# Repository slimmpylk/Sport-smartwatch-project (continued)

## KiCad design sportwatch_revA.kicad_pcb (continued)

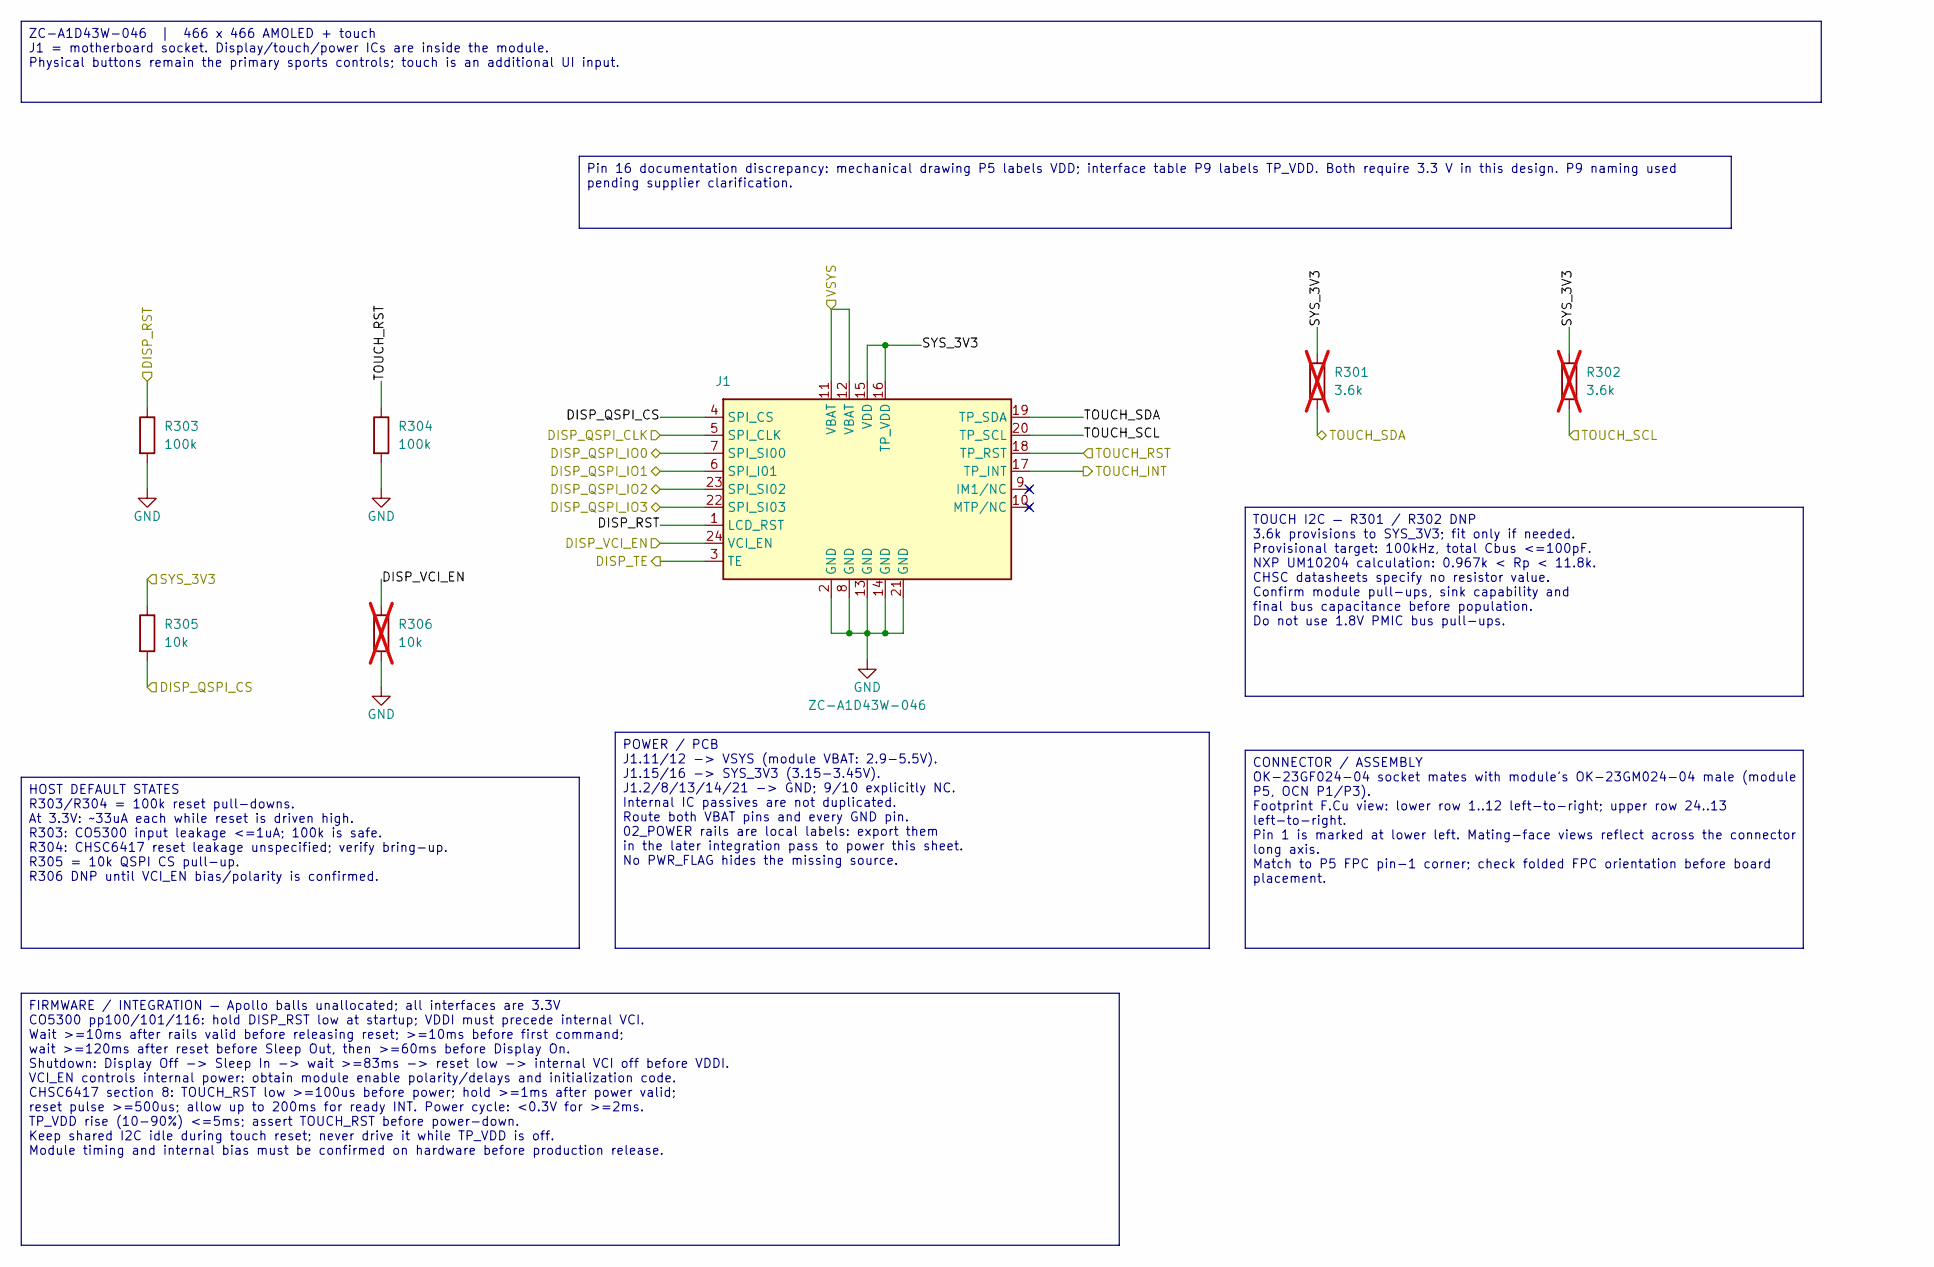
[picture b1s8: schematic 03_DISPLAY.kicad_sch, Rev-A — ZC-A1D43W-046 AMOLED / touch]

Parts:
J1: ZC-A1D43W-046; OK-23GF024-04; MPN OK-23GF024-04
R301, R302: 3.6k; R_0402_1005Metric; Tolerance 1%; Rating 0.063W, >=25V; not fitted
R303, R304: 100k; R_0402_1005Metric; Tolerance 1%; Rating 0.063W, >=25V
R305: 10k; R_0402_1005Metric; Tolerance 1%; Rating 0.063W, >=25V
R306: 10k; R_0402_1005Metric; Tolerance 1%; Rating 0.063W, >=25V; not fitted

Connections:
/DISP_QSPI_CLK: J1.5 (SPI_CLK); also elsewhere on the board
/DISP_QSPI_CS: J1.4 (SPI_CS), R305.2; also elsewhere on the board
/DISP_QSPI_IO0: J1.7 (SPI_SI00); also elsewhere on the board
/DISP_QSPI_IO1: J1.6 (SPI_I01); also elsewhere on the board
/DISP_QSPI_IO2: J1.23 (SPI_SI02); also elsewhere on the board
/DISP_QSPI_IO3: J1.22 (SPI_SI03); also elsewhere on the board
/DISP_RST: J1.1 (LCD_RST), R303.1; also elsewhere on the board
/DISP_TE: J1.3 (TE); also elsewhere on the board
/DISP_VCI_EN: J1.24 (VCI_EN), R306.1; also elsewhere on the board
/SYS_3V3: J1.15 (VDD), J1.16 (TP_VDD), R301.1, R302.1, R305.1; also elsewhere on the board
/TOUCH_INT: J1.17 (TP_INT); also elsewhere on the board
/TOUCH_RST: J1.18 (TP_RST), R304.1; also elsewhere on the board
/TOUCH_SCL: J1.20 (TP_SCL), R302.2; also elsewhere on the board
/TOUCH_SDA: J1.19 (TP_SDA), R301.2; also elsewhere on the board
/VSYS: J1.11 (VBAT), J1.12 (VBAT); also elsewhere on the board
GND: J1.2 (GND), J1.8 (GND), J1.13 (GND), J1.14 (GND), J1.21 (GND), R303.2, R304.2, R306.2; also elsewhere on the board

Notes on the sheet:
POWER / PCB J1.11/12 -> VSYS (module VBAT: 2.9-5.5V). J1.15/16 -> SYS_3V3 (3.15-3.45V). J1.2/8/13/14/21 -> GND; 9/10 explicitly NC. Internal IC passives are not duplicated. Route both VBAT pins and every GND pin. 02_POWER rails are local labels: export them in the later integration pass to power th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
CONNECTOR / ASSEMBLY OK-23GF024-04 socket mates with module's OK-23GM024-04 male (module P5, OCN P1/P3). Footprint F.Cu view: lower row 1..12 left-to-right; upper row 24..13 left-to-right. Pin 1 is marked at lower left. Mating-face views reflect across the connector long axis. Match to P5 FPC pin-1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
Pin 16 documentation discrepancy: mechanical drawing P5 labels VDD; interface table P9 labels TP_VDD. Both require 3.3 V in this design. P9 naming used pending supplier clarification.
ZC-A1D43W-046 | 466 x 466 AMOLED + touch J1 = motherboard socket. Display/touch/power ICs are inside the module. Physical buttons remain the primary sports controls; touch is an additional UI input.
TOUCH I2C — R301 / R302 DNP 3.6k provisions to SYS_3V3; fit only if needed. Provisional target: 100kHz, total Cbus <=100pF. NXP UM10204 calculation: 0.967k < Rp < 11.8k. CHSC datasheets specify no resistor value. Confirm module pull-ups, sink capability and final bus capacitance before population. 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
HOST DEFAULT STATES R303/R304 = 100k reset pull-downs. At 3.3V: ~33uA each while reset is driven high. R303: CO5300 input leakage <=1uA; 100k is safe. R304: CHSC6417 reset leakage unspecified; verify bring-up. R305 = 10k QSPI CS pull-up. R306 DNP until VCI_EN bias/polarity is confirmed.
FIRMWARE / INTEGRATION — Apollo balls unallocated; all interfaces are 3.3V CO5300 pp100/101/116: hold DISP_RST low at startup; VDDI must precede internal VCI. Wait >=10ms after rails valid before releasing reset; >=10ms before first command; wait >=120ms after reset before Sleep Out, then >=60ms be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

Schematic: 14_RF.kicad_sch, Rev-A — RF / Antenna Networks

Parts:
AE1401: ANT_BLE_2G4_TBD
AE1410: ANT_WIFI_2G4_5G_TBD
AE1420: ANT_GNSS_L1_L5_TBD
C1401: 18pF; C_0201_0603Metric
C1402: 2.8pF; C_0201_0603Metric
C1403: 3.2pF; C_0201_0603Metric
C1404: 1.0pF DNP; C_0201_0603Metric; not fitted
C1405: 220pF; C_0201_0603Metric
C1410, C1411, C1420, C1421: DNP; C_0201_0603Metric; not fitted
L1401: 1.5nH; L_0201_0603Metric
L1402: 1.8nH; L_0201_0603Metric
R1401: 0R (Lm2 tune); R_0201_0603Metric
R1410, R1420: 0R; R_0201_0603Metric
TP1401: BLE_RF_TEST_TBD
TP1410: WIFI_RF_TEST_TBD
TP1420: GNSS_RF_TEST_TBD

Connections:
/14_RF/BLE_RF_50R: AE1401.1, C1405.2, TP1401.1
/14_RF/GNSS_ANT_50R: AE1420.1, C1421.1, R1420.2, TP1420.1
/14_RF/WIFI_ANT_50R: AE1410.1, C1411.1, R1410.2, TP1410.1
/APOLLO_BLE_ANT: C1402.1, L1401.1, L1402.1; also elsewhere on the board
/APOLLO_BLE_AVDD_PA: C1401.1, L1401.2; also elsewhere on the board
/GNSS_RF: C1420.1, R1420.1; also elsewhere on the board
/WIFI_RF: C1410.1, R1410.1
GND: C1401.2, C1402.2, C1403.2, C1404.2, C1410.2, C1411.2, C1420.2, C1421.2; also elsewhere on the board
unnamed: C1403.1, L1402.2, R1401.1
unnamed: C1404.1, C1405.1, R1401.2

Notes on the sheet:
If the final 50-mm-class mechanics cannot support three independent antennas, BLE/Wi-Fi sharing may be reconsidered, but that requires a deliberate RF switch/diplexer redesign; do not silently merge the feeds.
Exact BLE/Wi-Fi/GNSS antennas are selected before routing is frozen, after the board outline, display, battery, case/bezel and available perimeter/ground-clearance regions are known.
Child-sheet labels APOLLO_BLE_ANT / APOLLO_BLE_AVDD_PA / WIFI_RF / GNSS_RF must be exported through the final hierarchy integration.
TP1401/TP1410/TP1420 are electrically attached RF test PROVISIONS; implement as tiny low-stub probe/coax-switch structures during PCB RF layout.
All RF paths must be controlled 50-ohm transmission lines with continuous reference ground, short feeds, via fencing where appropriate, and no unrelated routing through antenna keepouts.
MAX-F10S RF_IN is internally DC-blocked and requires a 50-ohm feed. No extra DC-block capacitor or active-antenna bias network is fitted for the passive Rev-A baseline.
BLE initial values are tuning STARTING POINTS only: LDC 1.5nH, Cdc1 18pF, Lm1 2.4nH, Cm1 2.0pF, Cm2 2.0pF, Cm3 DNP, Cc1 220pF. Final values require VNA/RF tuning on the real watch geometry.
nRF7002 Wi-Fi 2.4 / 5 GHz — WIFI_RF is already after the Nordic diplexer on 06_WIFI
14_RF — ANTENNA INTERFACES / MATCHING / TUNING — REV A
APOLLO510B BLE 2.4 GHz
BLE R1401 is the optional Lm2 position populated as 0R for Rev-A baseline; C1402 is on ANT/Lm1 input, C1403 at Lm1/Lm2 junction, C1404 DNP at Lm2 output.
Wi-Fi and GNSS use DNP/0R/DNP pi footprints so the antenna feed can be tuned without a PCB respin. Exact capacitor/series element values are selected after antenna and enclosure freeze.
Wi-Fi: 06_WIFI already combines nRF7002 TXRF0/TXRF1 through the Nordic 2.4/5GHz diplexer. 14_RF therefore starts from the single WIFI_RF feed.
Exact antenna MPNs/footprints are intentionally frozen only after case + PCB outline + battery + display geometry are known.
BLE: N1 BLE_ANT is single-ended RF; M1 BLE_AVDD_PA feeds the PA bias network. L1401/C1401 and the matching chain follow Ambiq's published initial BLE topology.
MAX-F10S GNSS L1/L5 — passive dual-band antenna baseline
Keep GNSS especially far from display clocks, Wi-Fi, switching regulators and haptic currents. Final antenna placements/keepouts are mechanical + RF decisions, not schematic-only decisions.

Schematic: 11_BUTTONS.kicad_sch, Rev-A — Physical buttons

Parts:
C1101, C1102, C1103, C1104, C1105: 47nF; C_0402_1005Metric
R1101, R1102, R1103, R1104, R1105: 100k; R_0402_1005Metric
SW1: BTN_LIGHT
SW2: BTN_UP
SW3: BTN_DOWN
SW4: BTN_START
SW5: BTN_BACK

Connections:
/BTN_BACK_N: C1105.1, R1105.2, SW5.1; also elsewhere on the board
/BTN_DOWN_N: C1103.1, R1103.2, SW3.1; also elsewhere on the board
/BTN_LIGHT_N: C1101.1, R1101.2, SW1.1; also elsewhere on the board
/BTN_START_N: C1104.1, R1104.2, SW4.1; also elsewhere on the board
/BTN_UP_N: C1102.1, R1102.2, SW2.1; also elsewhere on the board
GND: C1101.2, C1102.2, C1103.2, C1104.2, C1105.2, SW1.2, SW2.2, SW3.2, SW4.2, SW5.2; also elsewhere on the board
VOUT1_1V8: R1101.1, R1102.1, R1103.1, R1104.1, R1105.1; also elsewhere on the board

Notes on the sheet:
Switch footprints intentionally TBD until the exact sealed side-actuated tact switch / mechanical plunger stack is selected.
Each input has a 100k external pull-up to VOUT1_1V8 and 47nF hardware filter. Firmware should still debounce.
Apollo510B GPIO input leakage is max 20nA, so 100k pull-ups retain very large DC noise margin.
Do not rely on button labels as final GPIO ball assignments; those are frozen only during the Apollo integration pass.
100k + 47nF gives tau ~= 4.7ms (release threshold ~5.7ms for a 0.7*VDD GPIO VIH).
11_BUTTONS — FIVE PHYSICAL WATCH BUTTONS — ACTIVE LOW
No exposed electrical button contacts are assumed. If the final mechanical design creates an external conductive ESD path, add local ESD protection after mechanical review.
Final Apollo510B assignment: choose GPIOs valid in the selected low-power mode and configure falling-edge wake/interrupt.
Electrical behavior: unpressed = HIGH. Pressed = LOW. At 1.8V / 100k, a held button draws ~18uA.

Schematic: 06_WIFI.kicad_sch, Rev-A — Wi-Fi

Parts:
C601, C602, C606, C611: 4.7uF; C_0603_1608Metric
C603: 220nF; C_0201_0603Metric
C604, C614: 470nF; C_0201_0603Metric
C605, C610, C616, C619: 1.0uF; C_0402_1005Metric
C607, C618: 2.2uF; C_0603_1608Metric
C608: 10nF; C_0201_0603Metric
C609: 2.2uF; C_0402_1005Metric
C612, C617: 100nF; C_0201_0603Metric
C613: 22nF; C_0201_0603Metric
C615: 2.2uF; C_0201_0603Metric
L601: 3.3uH_1A_DCR<=200mR; L_2016_2016Metric
R601, R602: 100k; R_0402_1005Metric
U9: NRF7002-QFAA-R7; QFN48_6X6_NOR
U10: 2.4/5GHz_DIPLEXER_TBD
U11: TPS22918DBVT; SOT-23-6
Y1: NX1612SA-40M-EXS00A-CS14264; Crystal_1612-4Pin_1.6x1.2mm

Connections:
/06_WIFI/WIFI_IOVDD_1V8: C618.2, U9.48 (IOVDD), U11.6 (VOUT)
/06_WIFI/WIFI_PWRIOVDD: C609.2, C617.1, U9.1 (OTPVDD), U9.34 (PWRIOVDD)
/06_WIFI/WIFI_VDD_BUCK: C602.1, C603.1, C604.2, L601.2, U9.15 (RFBUCKVDD), U9.32 (PWRBUCKVDD)
/WIFI_BUCKEN: R601.1, U9.30 (BUCKEN); also elsewhere on the board
/WIFI_COEX_GRANT: U9.43 (COEX_GRANT); also elsewhere on the board
/WIFI_COEX_REQ: U9.42 (COEX_REQ); also elsewhere on the board
/WIFI_COEX_STATUS: U9.41 (COEX_STATUS0); also elsewhere on the board
/WIFI_HOST_IRQ: U9.46 (HOST_IRQ); also elsewhere on the board
/WIFI_IOVDD_EN: R602.2, U11.3 (ON); also elsewhere on the board
/WIFI_QSPI_CLK: U9.35 (QSPI_CLK); also elsewhere on the board
/WIFI_QSPI_CS: U9.36 (QSPI_SS); also elsewhere on the board
/WIFI_QSPI_IO0: U9.37 (QSPI_DATA0); also elsewhere on the board
/WIFI_QSPI_IO1: U9.38 (QSPI_DATA1); also elsewhere on the board
/WIFI_QSPI_IO2: U9.39 (QSPI_DATA2); also elsewhere on the board
/WIFI_QSPI_IO3: U9.40 (QSPI_DATA3); also elsewhere on the board
GND: C601.2, C602.2, C603.2, C604.1, C605.2, C606.2, C607.1, C608.2, C609.1, C610.1, C611.2, C612.2, C613.2, C614.2, C615.2, C616.2, C617.2, C618.1, C619.2, R601.2, R602.1, U9.27 (BUCKVSS), U9.28 (BUCKVSS), U9.47 (VSS), U9.49 (VSS), U10.2 (GND), U10.5 (GND), U10.7 (GND), U11.2 (GND), Y1.2 (GND), Y1.4 (GND); also elsewhere on the board
unnamed: C616.1, U9.19 (AFELDO)
unnamed: L601.1, U9.26 (BUCKOUT)
unnamed: C608.1, U9.29 (BUCKVMID)
unnamed: C610.2, U9.33 (DIGVDD)
unnamed: C611.1, U9.12 (PALDO)
unnamed: C612.1, U9.8 (PAVDD<1>), U9.10 (PAVDD<0>)
unnamed: C613.1, U9.14 (RFVDD)
unnamed: C614.1, U9.11 (SXLDO)
unnamed: C615.1, U9.16 (XOLDO)
unnamed: U9.18 (XON), Y1.3
unnamed: U9.17 (XOP), Y1.1
unnamed: U9.9 (TXRF<0>), U10.1 (2.4G)
unnamed: U9.7 (TXRF<1>), U10.3 (5G)
VBAT: C601.1, C605.1, C606.1, C607.2, U9.13 (VBAT), U9.20 (AFEVBAT), U9.25 (BUCKVBAT), U9.31 (BUCKVBATS); also elsewhere on the board
VOUT1_1V8: C619.1, U11.1 (VIN); also elsewhere on the board

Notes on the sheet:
QFN exposed pad pin49 + pin47 VSS are grounded. QFN48_6X6_NOR footprint must be audited before PCB layout.
U10: required 2.4/5 GHz WLAN diplexer; exact MPN/footprint TBD and selected together with 14_RF.
06_WIFI — nRF7002-QFAA-R7 DUAL-BAND WI-FI 6 — REV A
COEX_STATUS/REQ/GRANT kept for Wi-Fi/BLE coexistence; SW_CTRL0/1 NC with dedicated Wi-Fi antenna.
Nordic QFN reference capacitor values/package classes are reproduced; exact capacitor MPN/derating is checked at BOM/footprint audit.
IMPORTANT: nRF7002 main rail = protected-cell VBAT, NOT nPM1300 VSYS (VSYS can rise near 5 V on VBUS; nRF7002 VBAT recommended max 4.5 V).
WIFI_RF goes to 14_RF. Keep TXRF/diplexer/antenna path very short and copy Nordic RF layout closely.
C601/C602/C604/C608 ground returns must follow Nordic isolated-metal-plane guidance near the exposed paddle.
Use protected-cell VBAT for nRF7002 main supply. Do NOT substitute VSYS: nPM1300 can connect VSYS to ~5 V VBUS.
TPS22918 U11 switches 1.8 V IOVDD. QOD open; CT open. R602 and R601 hold IOVDD/BUCKEN off during Apollo reset.
Power sequence: VBAT present -> wait >=6 ms -> BUCKEN=1 -> wait >=1 ms -> IOVDD_EN=1. Power-down: BUCKEN=0 + IOVDD off before main battery rail disappears.
QSPI baseline, max interface clock 32 MHz. Final Apollo peripheral/ball allocation is deferred.
Wi-Fi must be disabled below nRF7002 VBAT minimum 2.9 V. Battery target is nominal 3.7 V / ~4.2 V full.
Nordic QFN reference network / QSPI host / 3-wire BLE coexistence / dedicated Wi-Fi antenna baseline
Y1: 40 MHz, SMD1612, CL=8 pF, ESR <=100 ohm. Exact crystal MPN/footprint TBD.
U10 is still a placeholder: current symbol pins 2/5/7 are grounded. Confirm COM, 2.4G, 5G and all GND pad numbers against the selected diplexer datasheet before PCB freeze.

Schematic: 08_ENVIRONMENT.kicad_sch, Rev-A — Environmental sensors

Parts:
C801, C802, C803, C804: 100nF; C_0402_1005Metric
R801, R802: 4.7k; R_0402_1005Metric
R803: 10k; R_0402_1005Metric
U4: BMP585; LGA9_BMP585_BOS
U5: OPT4001DTSR; DTS0008A-MFG
U6: MAX30208CLB+T; 21-100265_MXM

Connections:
ALS_INT: R803.2, U5.7 (INT); also elsewhere on the board
BARO_INT: U4.5 (INT); also elsewhere on the board
ENV_I2C_SCL: R802.2, U4.1 (SCX), U5.5 (SCL); also elsewhere on the board
ENV_I2C_SDA: R801.2, U4.2 (SDX), U5.8 (SDA), U6.8 (SDA); also elsewhere on the board
GND: C801.2, C802.2, C803.2, C804.2, U4.3 (SDO), U4.6 (VSS), U5.2 (ADDR), U5.4 (GND), U6.4 (GND), U6.5 (GND), U6.6 (GND), U6.7 (GPIO1), U6.10 (GPIO0); also elsewhere on the board
VOUT1_1V8: C801.1, C802.1, C803.1, C804.1, R801.1, R802.1, R803.1, U4.4 (VDDIO), U4.7 (CSB), U4.8 (VDD), U5.1 (VDD), U6.1 (VDD), U6.2 (VDD), U6.3 (VDD); also elsewhere on the board

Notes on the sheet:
POWER / BUS PULL-UPS
R801/R802 = 4.7k pull-ups for provisional 400 kHz short sensor bus. Consolidate pull-ups if this bus is later shared with BMM350/PMIC.
MAX30208: GPIO1=GND and GPIO0=GND => fixed 7-bit address 0x50; temperature is polled, no interrupt pin consumed.
BMP585 mechanical: pressure port must breathe through a hydrophobic/ePTFE vent; never cover the port with adhesive or conformal coating.
08_ENVIRONMENT — BMP585 BAROMETER + MAX30208 SKIN TEMPERATURE + OPT4001 AMBIENT LIGHT — REV A
OPT4001 mechanical: provide a real optical window / bezel opening; do not place behind opaque AMOLED or black mask.
All three sensors use VOUT1_1V8. ENV_I2C_SDA/SCL are a 1.8 V I2C bus; Apollo pin assignment is deferred.
OPT4001DTSR: ADDR=GND => 0x44; ALS_INT is open-drain and uses R803=10k pull-up. C801=100nF at VDD.
MAX30208 placement: skin-facing and thermally isolated from PMIC/SoC/PPG LEDs; thin traces/cutouts or flex improve skin tracking.
BMP585: I2C mode; CSB=1.8 V, SDO=GND => 7-bit address 0x46; BARO_INT reserved for data-ready/interrupt.
BMP585: C803/C804 = 100nF at VDDIO/VDD. If either rail ramps faster than 10 us, Bosch recommends 10 ohm series limiting.

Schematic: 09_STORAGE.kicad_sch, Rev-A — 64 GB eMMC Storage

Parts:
C901: 4.7uF; C_0603_1608Metric
C902: 220nF; C_0402_1005Metric
C903: 2.2uF; C_0603_1608Metric
C904, C906: 100nF; C_0402_1005Metric
C905: 1.0uF; C_0402_1005Metric
R901: 10k; R_0402_1005Metric
R902, R903, R904, R905, R906, R907, R908, R909, R910: 47k; R_0402_1005Metric
U901: EMMC64G-TB9F-06011; FBGA-153_8.0x8.5mm_Layout14x14_P0.5mm

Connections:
/09_STORAGE/EMMC_VDDI: C905.1, C906.1, U901.C2 (VDDI)
/EMMC_CLK: U901.M6 (CLK); also elsewhere on the board
/EMMC_CMD: R901.2, U901.M5 (CMD); also elsewhere on the board
/EMMC_DAT0: R902.2, U901.A3 (DAT0); also elsewhere on the board
/EMMC_DAT1: R903.2, U901.A4 (DAT1); also elsewhere on the board
/EMMC_DAT2: R904.2, U901.A5 (DAT2); also elsewhere on the board
/EMMC_DAT3: R905.2, U901.B2 (DAT3); also elsewhere on the board
/EMMC_DAT4: R906.2, U901.B3 (DAT4); also elsewhere on the board
/EMMC_DAT5: R907.2, U901.B4 (DAT5); also elsewhere on the board
/EMMC_DAT6: R908.2, U901.B5 (DAT6); also elsewhere on the board
/EMMC_DAT7: R909.2, U901.B6 (DAT7); also elsewhere on the board
/EMMC_RST_N: R910.2, U901.K5 (~RST_n); also elsewhere on the board
/VOUT2_3V0_PROVISIONAL: C901.1, C902.1, U901.E6 (VCC), U901.F5 (VCC), U901.J10 (VCC), U901.K9 (VCC); also elsewhere on the board
GND: C901.2, C902.2, C903.2, C904.2, C905.2, C906.2, U901.A6 (VSS), U901.C4 (VSSQ), U901.E7 (VSS), U901.G5 (VSS), U901.H10 (VSS), U901.J5 (VSS), U901.K8 (VSS), U901.N2 (VSSQ), U901.N5 (VSSQ), U901.P4 (VSSQ), U901.P6 (VSSQ); also elsewhere on the board
VOUT1_1V8: C903.1, C904.1, R901.1, R902.1, R903.1, R904.1, R905.1, R906.1, R907.1, R908.1, R909.1, R910.1, U901.C6 (VCCQ), U901.M4 (VCCQ), U901.N4 (VCCQ), U901.P3 (VCCQ), U901.P5 (VCCQ); also elsewhere on the board

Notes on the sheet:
RFU/VSF/NC balls remain unconnected exactly as Kingston requires. Footprint is intentionally still unassigned pending the dedicated FBGA153 footprint audit.
Kingston states DAT1-DAT7 internal pull-ups are disconnected after entering wide-bus modes, so external biasing remains useful.
Kingston's public datasheet calls for an external VDDI Creg but refers exact design values to a separate design guide; capacitor values use standard eMMC guidance.
09_STORAGE — 64 GB eMMC / APOLLO510B SDIO0 8-BIT — REV A
Architecture: Apollo510B SDIO0 is reserved for this eMMC because SDIO0 supports the full 8-bit eMMC bus.
EMMC_RST_N uses a normal Apollo GPIO; hardware reset is disabled by default in eMMC and must be enabled through EXT_CSD if used.
Add/tune a small CLK source-series resistor near Apollo during 01_APOLLO integration (22 ohm initial target); keep it physically at the host, not beside U1.
Apollo510B documents SDIO0 up to 96 MHz / 96 MB/s. Therefore U1 is NOT operated in HS400; H5/DS is intentionally NC.
Place U1 close to Apollo. Route CLK/CMD/DAT0..7 as controlled-impedance short traces with a continuous reference plane; length/skew review occurs in PCB phase.
U1 custom FBGA153 ball map verified against Kingston Table 9 before wiring.
VCC = VOUT2_3V0_PROVISIONAL. Kingston allows 2.7-3.6 V; 3.0 V reduces load on the separate display 3.3 V rail.
C901/C902: VCC 4.7uF + 220nF. C903/C904: VCCQ 2.2uF + 100nF. C905/C906: VDDI 1uF + 100nF.
Reserve Apollo SDIF0 signals: DAT0..3 on GPIO84..87, CLK on GPIO88, DAT4..7 on GPIO156..159, CMD on GPIO160.
VCCQ = VOUT1_1V8. This keeps the complete SDIO0 bus in the 1.8 V I/O domain and preserves high-speed compatibility.
R901=10k CMD, R902-R909=47k DAT0..7, R910=47k reset pull-ups; all are explicitly connected to VOUT1_1V8.
VOUT rails and host labels are still local to this child sheet until final hierarchical integration.

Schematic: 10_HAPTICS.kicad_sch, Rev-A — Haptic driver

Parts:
C1001, C1002: 100nF; C_0402_1005Metric
LRA1: LRA_TBD
R1001, R1002: 2.2k; R_0402_1005Metric
R1003: 220k; R_0402_1005Metric
R1004: 2.2k; R_0402_1005Metric; not fitted
U7: DRV2625YFFR; YFF0009AHAN

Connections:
/10_HAPTICS/HAPTIC_REG: C1002.1, U7.A2 (REG)
/HAPTIC_I2C_SCL: R1002.2, U7.C1 (SCL); also elsewhere on the board
/HAPTIC_I2C_SDA: R1001.2, U7.B1 (SDA); also elsewhere on the board
/HAPTIC_NRST: R1003.1, U7.B2 (NRST); also elsewhere on the board
/HAPTIC_TRIG_INTZ: R1004.2, U7.A1 (TRIG_INTZ); also elsewhere on the board
/VSYS: C1001.1, U7.C2 (VDD); also elsewhere on the board
GND: C1001.2, C1002.2, R1003.2, U7.B3 (GND); also elsewhere on the board
unnamed: LRA1.1 (OUT+), U7.A3 (OUT+)
unnamed: LRA1.2 (OUT-), U7.C3 (OUT-)
VOUT1_1V8: R1001.1, R1002.1, R1004.1; also elsewhere on the board

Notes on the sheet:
I2C address: fixed 7-bit 0x5A. R1001/R1002 = 2.2k to 1.8 V; consolidate/DNP if this bus is later shared.
TRIG/INTZ has an internal pull-down. R1004 is DNP and is only populated if firmware uses TRIG/INTZ as an interrupt output.
DRV2625 footprint imported as YFF0009AHAN; verify WLCSP/DSBGA land pattern and ball orientation during the dedicated footprint audit.
10_HAPTICS — DRV2625 CLOSED-LOOP HAPTIC DRIVER + LRA — REV A
VSYS and 1.8 V labels are still child-sheet-local until the root hierarchy integration pass.
NRST high threshold is 1.41 V, so Apollo 1.8 V GPIO drive is valid. R1003 keeps DRV2625 in shutdown during host reset/boot.
Exact LRA part and mechanical mounting are intentionally TBD; select before PCB mechanical freeze.
Mechanical/layout: place LRA away from BMM350 magnetometer, GNSS antenna and PPG analog front end; mechanically couple it to the case.
C1001 (VDD) and C1002 (REG) are both 100nF as required by TI. Never use REG to power another circuit.
LRA1 is electrically differential between OUT+ and OUT-. Do not add a flyback diode across the actuator.
DRV2625 VDD is powered from VSYS (2.7–5.5 V requirement). Logic/control bus is 1.8 V.

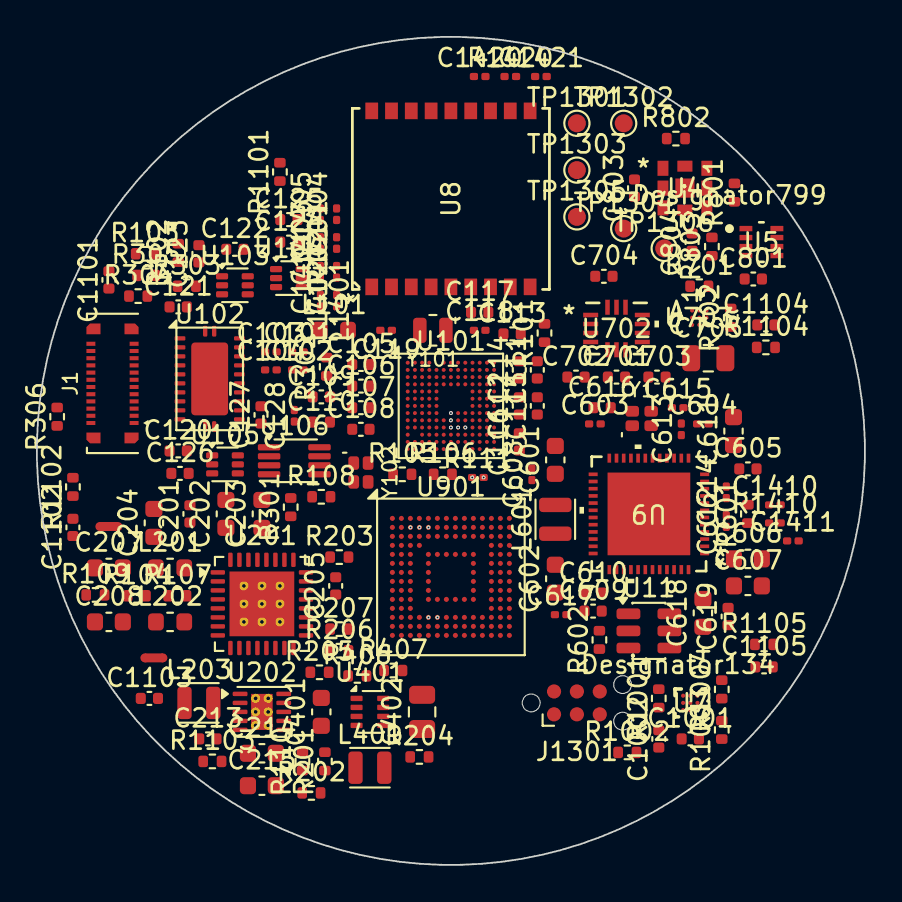
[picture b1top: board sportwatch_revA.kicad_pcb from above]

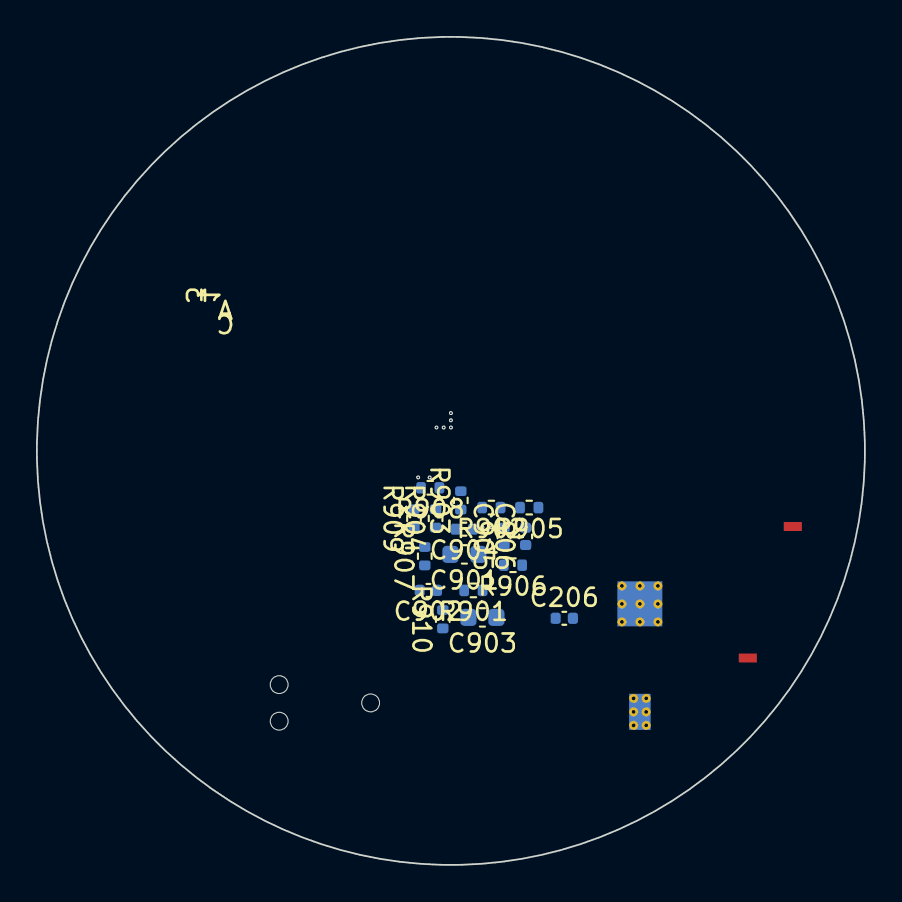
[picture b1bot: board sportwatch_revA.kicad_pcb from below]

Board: 8 copper layers, 46.0 x 46.0 mm, 184 parts (17 on the bottom side), 145 nets.

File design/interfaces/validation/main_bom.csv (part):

Reference,Value,Footprint,Board,DNP,SelectionStatus
AE1401,ANT_BLE_2G4_TBD,,MAIN,False,BASELINE
AE1410,ANT_WIFI_2G4_5G_TBD,,MAIN,False,BASELINE
AE1420,ANT_GNSS_L1_L5_TBD,,MAIN,False,BASELINE
C1001,100nF,Capacitor_SMD:C_0402_1005Metric,MAIN,False,BASELINE
C1002,100nF,Capacitor_SMD:C_0402_1005Metric,MAIN,False,BASELINE
C101,4.7uF,Capacitor_SMD:C_0201_0603Metric,MAIN,False,BASELINE
C102,4.7uF,Capacitor_SMD:C_0201_0603Metric,MAIN,False,BASELINE
C103,4.7uF,Capacitor_SMD:C_0201_0603Metric,MAIN,False,BASELINE
C104,4.7uF,Capacitor_SMD:C_0201_0603Metric,MAIN,False,BASELINE
C105,10uF,Capacitor_SMD:C_0402_1005Metric,MAIN,False,BASELINE
C106,1uF,Capacitor_SMD:C_0402_1005Metric,MAIN,False,BASELINE
C107,2.2uF,Capacitor_SMD:C_0402_1005Metric,MAIN,False,BASELINE
C108,2.2uF,Capacitor_SMD:C_0402_1005Metric,MAIN,False,BASELINE
C109,2.2uF,Capacitor_SMD:C_0402_1005Metric,MAIN,False,BASELINE
C110,4.7uF,Capacitor_SMD:C_0402_1005Metric,MAIN,False,BASELINE
C1101,47nF,Capacitor_SMD:C_0402_1005Metric,MAIN,False,BASELINE
C1102,47nF,Capacitor_SMD:C_0402_1005Metric,MAIN,False,BASELINE
C1103,47nF,Capacitor_SMD:C_0402_1005Metric,MAIN,False,BASELINE
C1104,47nF,Capacitor_SMD:C_0402_1005Metric,MAIN,False,BASELINE
C1105,47nF,Capacitor_SMD:C_0402_1005Metric,MAIN,False,BASELINE
C111,100nF,Capacitor_SMD:C_0402_1005Metric,MAIN,False,BASELINE
C112,2.2uF,Capacitor_SMD:C_0402_1005Metric,MAIN,False,BASELINE
C113,100nF,Capacitor_SMD:C_0402_1005Metric,MAIN,False,BASELINE
C114,2.2uF,Capacitor_SMD:C_0402_1005Metric,MAIN,False,BASELINE
C115,100nF,Capacitor_SMD:C_0402_1005Metric,MAIN,False,BASELINE
C116,1.0uF,Capacitor_SMD:C_0402_1005Metric,MAIN,False,BASELINE
C117,2.2uF,Capacitor_SMD:C_0402_1005Metric,MAIN,False,BASELINE
C118,8.2pF,Capacitor_SMD:C_0201_0603Metric,MAIN,False,BASELINE
C119,8.2pF,Capacitor_SMD:C_0201_0603Metric,MAIN,False,BASELINE
C120,100nF,Capacitor_SMD:C_0402_1005Metric,MAIN,False,BASELINE
C121,100nF,Capacitor_SMD:C_0402_1005Metric,MAIN,False,BASELINE
C122,100nF,Capacitor_SMD:C_0402_1005Metric,MAIN,False,BASELINE
C123,100nF,Capacitor_SMD:C_0402_1005Metric,MAIN,False,BASELINE
C124,100nF,Capacitor_SMD:C_0402_1005Metric,MAIN,False,BASELINE
C125,100nF,Capacitor_SMD:C_0402_1005Metric,MAIN,False,BASELINE
C126,100nF,Capacitor_SMD:C_0402_1005Metric,MAIN,False,BASELINE
C127,100nF,Capacitor_SMD:C_0402_1005Metric,MAIN,False,BASELINE
C128,100pF,Capacitor_SMD:C_0201_0603Metric,MAIN,False,BASELINE
C1401,18pF,Capacitor_SMD:C_0201_0603Metric,MAIN,False,BASELINE
C1402,2.8pF,Capacitor_SMD:C_0201_0603Metric,MAIN,False,BASELINE
C1403,3.2pF,Capacitor_SMD:C_0201_0603Metric,MAIN,False,BASELINE
C1404,1.0pF DNP,Capacitor_SMD:C_0201_0603Metric,MAIN,True,BASELINE
C1405,220pF,Capacitor_SMD:C_0201_0603Metric,MAIN,False,BASELINE
C1410,DNP,Capacitor_SMD:C_0201_0603Metric,MAIN,True,BASELINE
C1411,DNP,Capacitor_SMD:C_0201_0603Metric,MAIN,True,BASELINE
C1420,DNP,Capacitor_SMD:C_0201_0603Metric,MAIN,True,BASELINE
C1421,DNP,Capacitor_SMD:C_0201_0603Metric,MAIN,True,BASELINE
C201,1uF,Capacitor_SMD:C_0402_1005Metric,MAIN,False,BASELINE
C202,10uF,Capacitor_SMD:C_0603_1608Metric,MAIN,False,BASELINE
C203,10uF,Capacitor_SMD:C_0603_1608Metric,MAIN,False,BASELINE
C204,10uF,Capacitor_SMD:C_0603_1608Metric,MAIN,False,BASELINE
C205,1uF,Capacitor_SMD:C_0402_1005Metric,MAIN,False,BASELINE
C206,2.2uF,Capacitor_SMD:C_0402_1005Metric,MAIN,False,BASELINE
C207,10uF,Capacitor_SMD:C_0603_1608Metric,MAIN,False,BASELINE
C208,10uF,Capacitor_SMD:C_0603_1608Metric,MAIN,False,BASELINE
C213,100nF,Capacitor_SMD:C_0402_1005Metric,MAIN,False,BASELINE
C214,10uF,Capacitor_SMD:C_0603_1608Metric,MAIN,False,BASELINE
C215,22uF,Capacitor_SMD:C_0603_1608Metric,MAIN,False,BASELINE
C401,22uF,Capacitor_SMD:C_0603_1608Metric,MAIN,False,BASELINE
C402,47uF,Capacitor_SMD:C_0805_2012Metric,MAIN,False,BASELINE
C601,4.7uF,Capacitor_SMD:C_0603_1608Metric,MAIN,False,BASELINE
C602,4.7uF,Capacitor_SMD:C_0603_1608Metric,MAIN,False,BASELINE
C603,220nF,Capacitor_SMD:C_0201_0603Metric,MAIN,False,BASELINE
C604,470nF,Capacitor_SMD:C_0201_0603Metric,MAIN,False,BASELINE
C605,1.0uF,Capacitor_SMD:C_0402_1005Metric,MAIN,False,BASELINE
C606,4.7uF,Capacitor_SMD:C_0603_1608Metric,MAIN,False,BASELINE
C607,2.2uF,Capacitor_SMD:C_0603_1608Metric,MAIN,False,BASELINE
C608,10nF,Capacitor_SMD:C_0201_0603Metric,MAIN,False,BASELINE
C609,2.2uF,Capacitor_SMD:C_0402_1005Metric,MAIN,False,BASELINE
C610,1.0uF,Capacitor_SMD:C_0402_1005Metric,MAIN,False,BASELINE
C611,4.7uF,Capacitor_SMD:C_0603_1608Metric,MAIN,False,BASELINE
C612,100nF,Capacitor_SMD:C_0201_0603Metric,MAIN,False,BASELINE
C613,22nF,Capacitor_SMD:C_0201_0603Metric,MAIN,False,BASELINE
C614,470nF,Capacitor_SMD:C_0201_0603Metric,MAIN,False,BASELINE
C615,2.2uF,Capacitor_SMD:C_0201_0603Metric,MAIN,False,BASELINE
C616,1.0uF,Capacitor_SMD:C_0402_1005Metric,MAIN,False,BASELINE
C617,100nF,Capacitor_SMD:C_0201_0603Metric,MAIN,False,BASELINE
C618,2.2uF,Capacitor_SMD:C_0603_1608Metric,MAIN,False,BASELINE
C619,1.0uF,Capacitor_SMD:C_0402_1005Metric,MAIN,False,BASELINE
C701,100nF,Capacitor_SMD:C_0402_1005Metric,MAIN,False,BASELINE
C702,100nF,Capacitor_SMD:C_0402_1005Metric,MAIN,False,BASELINE
C703,100nF,Capacitor_SMD:C_0402_1005Metric,MAIN,False,BASELINE
C704,100nF,Capacitor_SMD:C_0402_1005Metric,MAIN,False,BASELINE
C705,2.2uF,Capacitor_SMD:C_0805_2012Metric,MAIN,False,BASELINE
C801,100nF,Capacitor_SMD:C_0402_1005Metric,MAIN,False,BASELINE
C803,100nF,Capacitor_SMD:C_0402_1005Metric,MAIN,False,BASELINE
C804,100nF,Capacitor_SMD:C_0402_1005Metric,MAIN,False,BASELINE
C901,4.7uF,Capacitor_SMD:C_0603_1608Metric,MAIN,False,BASELINE
C902,220nF,Capacitor_SMD:C_0402_1005Metric,MAIN,False,BASELINE
C903,2.2uF,Capacitor_SMD:C_0603_1608Metric,MAIN,False,BASELINE
C904,100nF,Capacitor_SMD:C_0402_1005Metric,MAIN,False,BASELINE
C905,1.0uF,Capacitor_SMD:C_0402_1005Metric,MAIN,False,BASELINE
C906,100nF,Capacitor_SMD:C_0402_1005Metric,MAIN,False,BASELINE
D1201,ESD_TVS_RATING_MPN_TBD,,MAIN,False,PROVISIONAL - MPN and footprint TBD
J1,ZC-A1D43W-046,sportwatch_custom:OK-23GF024-04,MAIN,False,BASELINE
J1301,TC2030-CTX-NL_TARGET,Connector:Tag-Connect_TC2030-IDC-NL_2x03_P1.27mm_Vertical,MAIN,False,BASELINE
J1501,SENSOR_24_ABSTRACT,,MAIN,False,PROVISIONAL - MPN and footprint TBD
J201,BATTERY_3PIN,,MAIN,False,BASELINE
J202,CHARGER_HARNESS_TBD,,MAIN,False,PROVISIONAL - MPN and footprint TBD
L101,2.2uH / Isat>=1A / DCR<550mR,Inductor_SMD:L_0603_1608Metric,MAIN,False,BASELINE
L1401,1.5nH,Inductor_SMD:L_0201_0603Metric,MAIN,False,BASELINE
L1402,1.8nH,Inductor_SMD:L_0201_0603Metric,MAIN,False,BASELINE
L201,2.2uH,Inductor_SMD:L_0603_1608Metric,MAIN,False,BASELINE
L202,2.2uH,Inductor_SMD:L_0603_1608Metric,MAIN,False,BASELINE
L203,2.2uH,sportwatch_custom:L_2016_2016Metric,MAIN,False,BASELINE
L401,1uH,sportwatch_custom:L_2016_2016Metric,MAIN,False,BASELINE
L601,3.3uH_1A_DCR<=200mR,sportwatch_custom:L_2016_2016Metric,MAIN,False,BASELINE
LRA1,LRA_TBD,,MAIN,False,BASELINE
NT201,NetTie_2,NetTie:NetTie-2_SMD_Pad0.5mm,MAIN,False,BASELINE
NT202,NetTie_2,NetTie:NetTie-2_SMD_Pad0.5mm,MAIN,False,BASELINE
R1001,2.2k,Resistor_SMD:R_0402_1005Metric,MAIN,False,BASELINE
R1002,2.2k,Resistor_SMD:R_0402_1005Metric,MAIN,False,BASELINE
R1003,220k,Resistor_SMD:R_0402_1005Metric,MAIN,False,BASELINE
R1004,2.2k,Resistor_SMD:R_0402_1005Metric,MAIN,True,BASELINE
R101,10M,Resistor_SMD:R_0402_1005Metric,MAIN,False,BASELINE
R102,100k,Resistor_SMD:R_0402_1005Metric,MAIN,False,BASELINE
R103,100k,Resistor_SMD:R_0402_1005Metric,MAIN,False,BASELINE
R104,4.7k,Resistor_SMD:R_0402_1005Metric,MAIN,False,BASELINE
R105,4.7k,Resistor_SMD:R_0402_1005Metric,MAIN,False,BASELINE
R106,4.7k,Resistor_SMD:R_0402_1005Metric,MAIN,False,BASELINE
R107,4.7k,Resistor_SMD:R_0402_1005Metric,MAIN,False,BASELINE
R108,200k,Resistor_SMD:R_0402_1005Metric,MAIN,False,BASELINE
R109,300k,Resistor_SMD:R_0402_1005Metric,MAIN,False,BASELINE
R110,10k,Resistor_SMD:R_0402_1005Metric,MAIN,False,BASELINE
R1101,100k,Resistor_SMD:R_0402_1005Metric,MAIN,False,BASELINE
R1102,100k,Resistor_SMD:R_0402_1005Metric,MAIN,False,BASELINE
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
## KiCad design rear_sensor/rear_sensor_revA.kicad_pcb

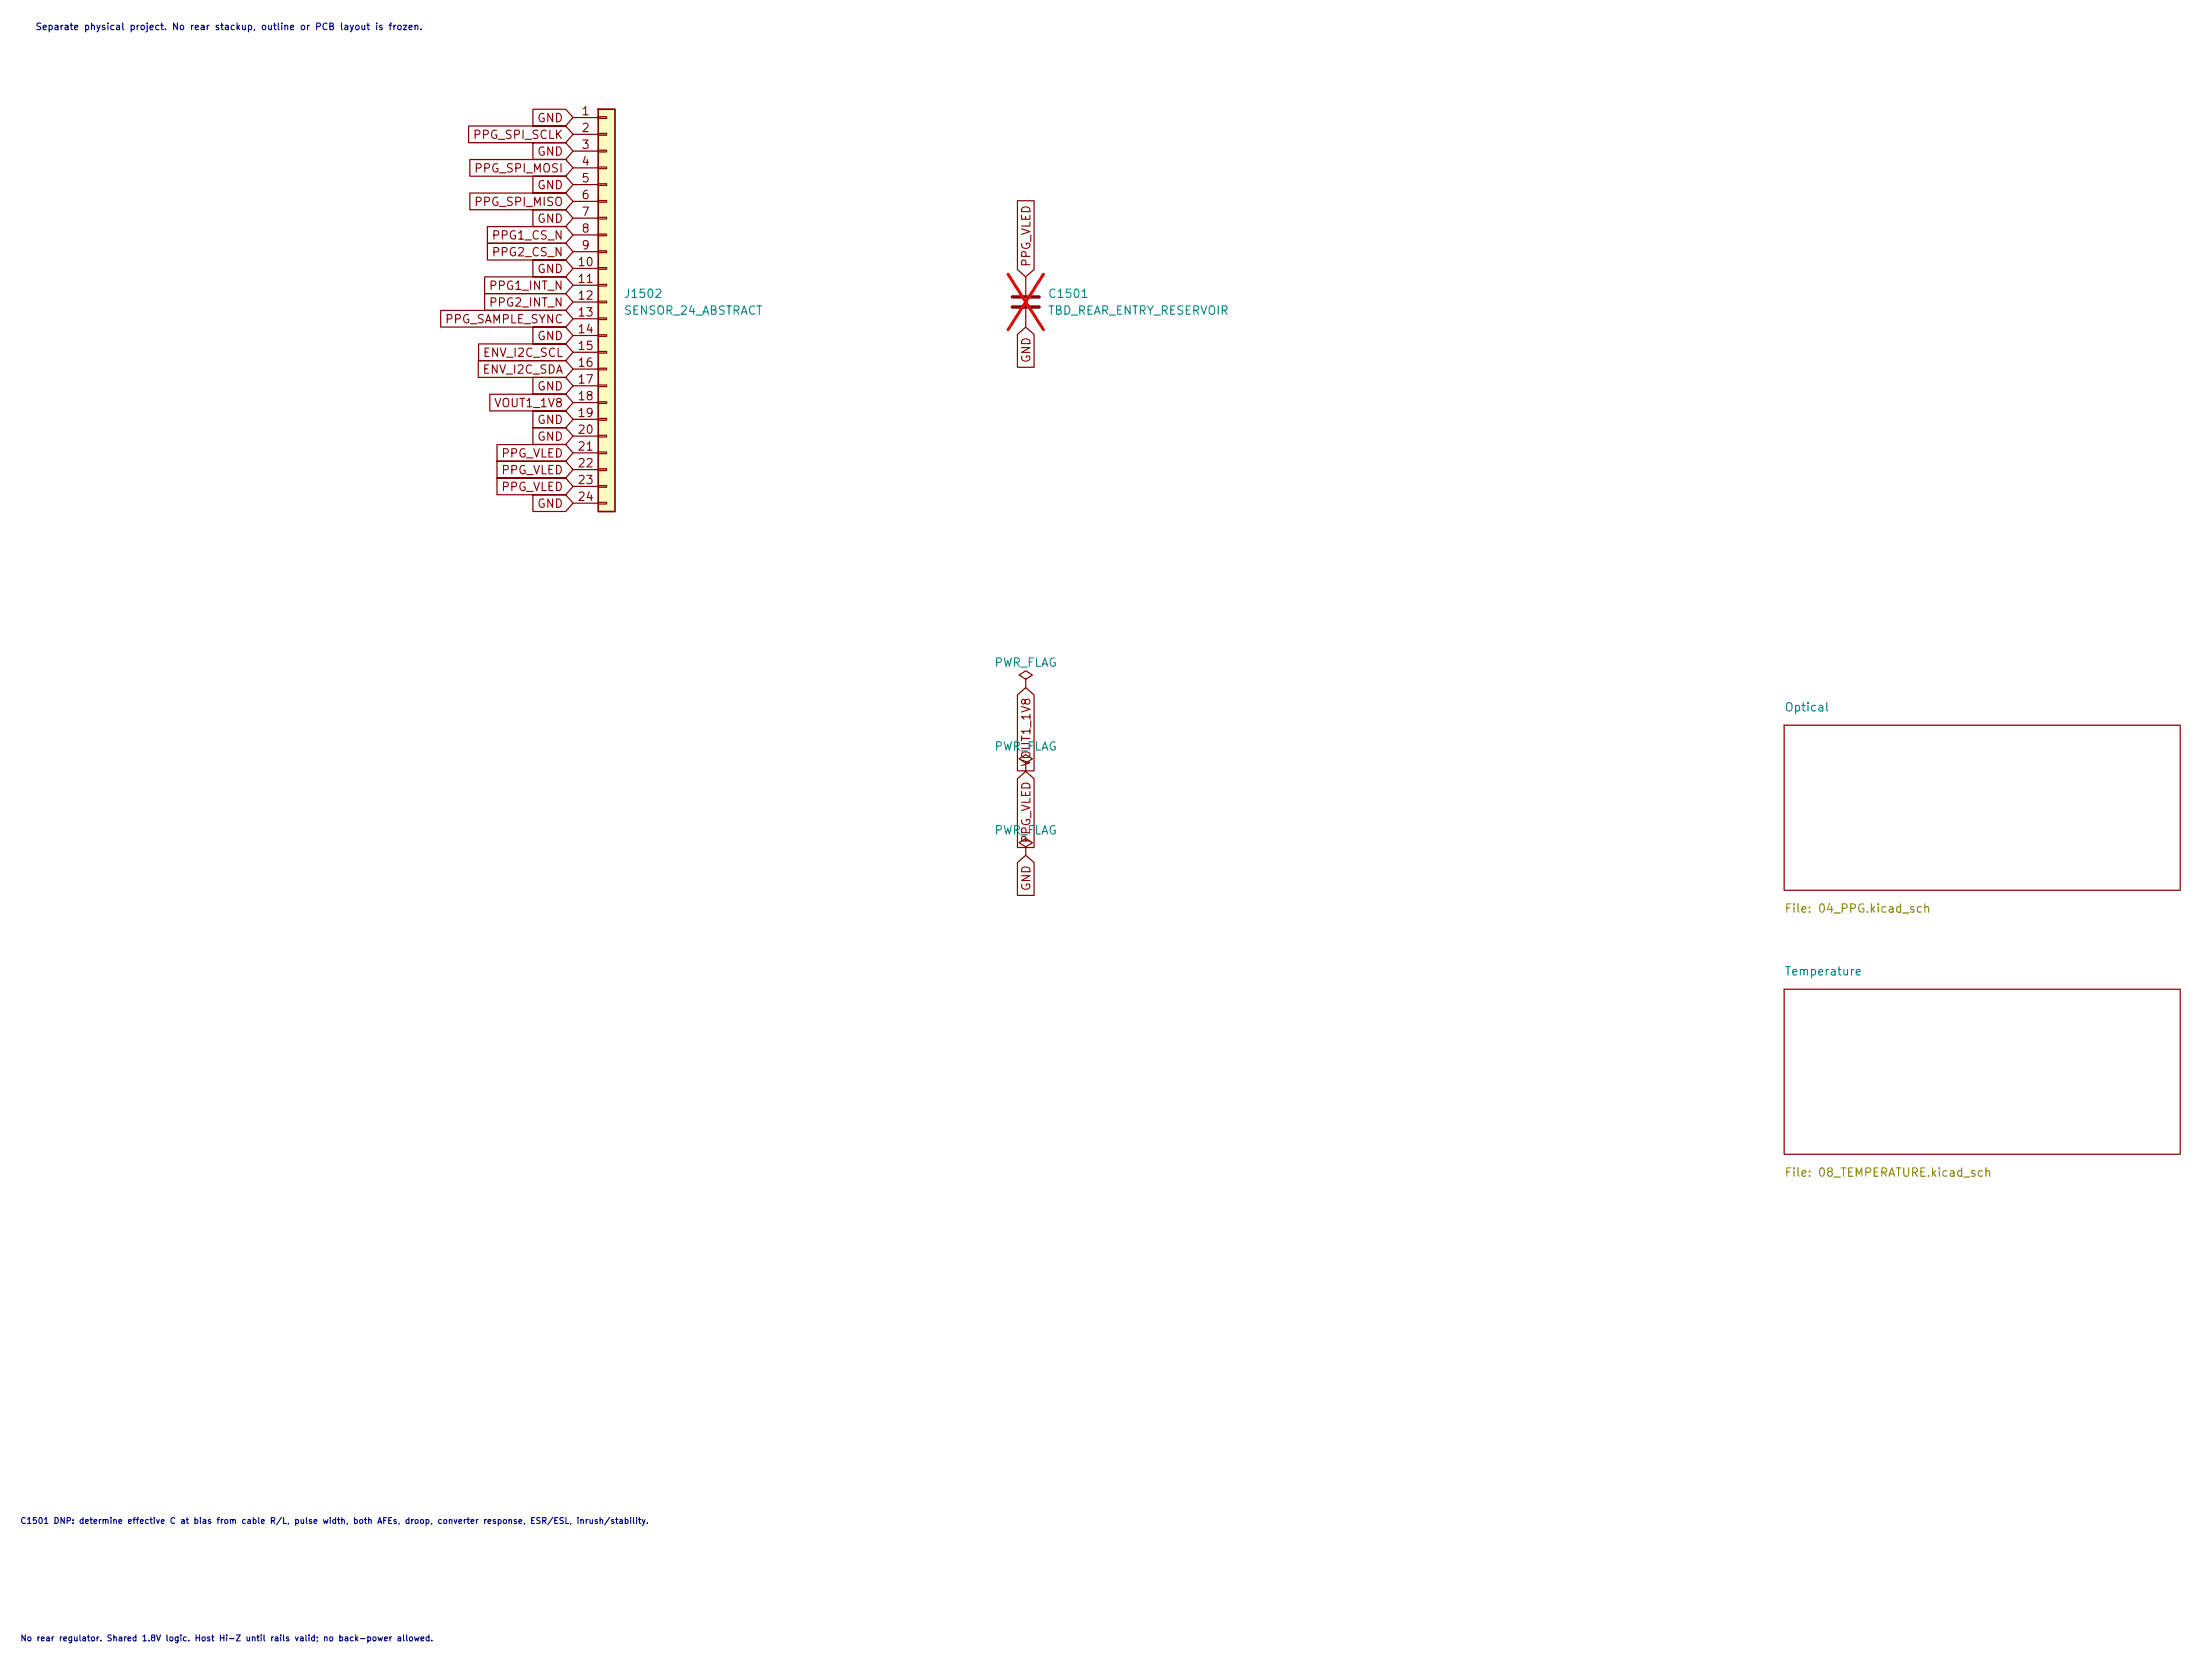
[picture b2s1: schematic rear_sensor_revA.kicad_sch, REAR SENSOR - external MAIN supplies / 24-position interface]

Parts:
C1501: TBD_REAR_ENTRY_RESERVOIR; not fitted
J1502: SENSOR_24_ABSTRACT

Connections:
unnamed: C1501.1, J1502.21, J1502.22, J1502.23
unnamed: C1501.2, J1502.1, J1502.3, J1502.5, J1502.7, J1502.10, J1502.14, J1502.17, J1502.19, J1502.20, J1502.24

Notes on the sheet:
Separate physical project. No rear stackup, outline or PCB layout is frozen.
C1501 DNP: determine effective C at bias from cable R/L, pulse width, both AFEs, droop, converter response, ESR/ESL, inrush/stability.
No rear regulator. Shared 1.8V logic. Host Hi-Z until rails valid; no back-power allowed.
